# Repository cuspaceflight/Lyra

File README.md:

# Lyra

## Build Instructions
### With nix

Run
```
nix build
```
which should download the required packages and build the program, placing
the built packages in `result` by default

### Other
Requires `pico-sdk`

```
cmake -DPICO_SDK_PATH='PICO_SDK_PATH' -B build .
cmake --build build
```
which should generate `build/src/Lyra.uf2`

### Logger

The logger can be enabled through additional flags that can
be set in cmake

```
-DLOG_ENABLE=1 # Enable the Logger
-DLOG_LEVEL=LOG_LEVEL_{VERBOSE|INFO|DEBUG|ERROR|CRITICAL} # Set the logging level
-DLOG_ENABLE_COLOUR=1 # Enable colours in the output
```

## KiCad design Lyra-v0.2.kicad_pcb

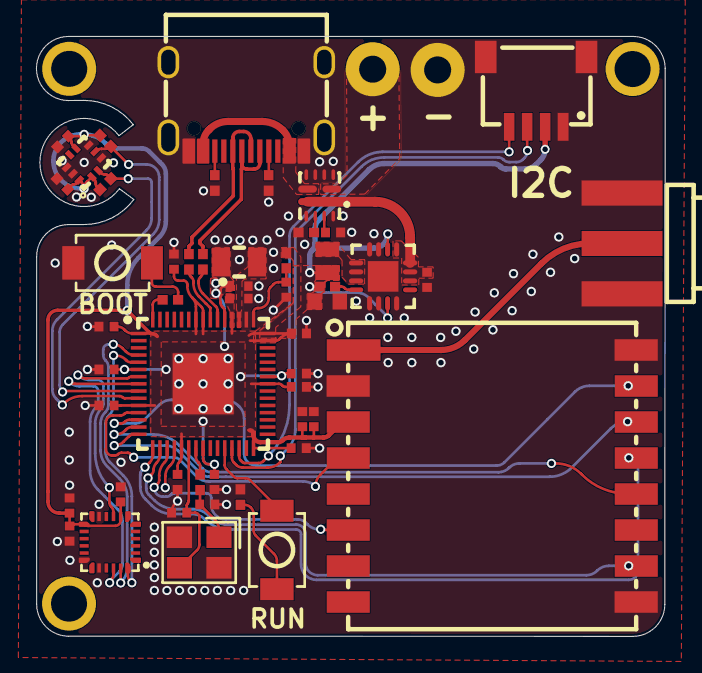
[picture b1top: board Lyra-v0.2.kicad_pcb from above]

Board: 4 copper layers, 34.9 x 33.3 mm, 54 parts (0 on the bottom side), 40 nets.

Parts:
C1, C11: 4.7uF; C0402
C2, C3, C4, C5, C6, C7, C8, C9, C10, C16, C19, C22, C23, C25: 100nF; C0402
C12, C13: 4.7uF; C0402_WIDE
C14, C15: 15pF; C0402
C17, C24: 10uF; C0402
C18: 22uF; C0603
C20: 10nF; C0402
C21: 2.2uF; C0402
CN1: QWIIC; CONN-SMD_4P-P1.00_SM04B-SRSS-TB-LF-SN
L1: 3.3uH; IND-SMD_L2.0-W1.6_AOTA-B201610S3R3-101-T
L2: RA-01SH; WIRELM-SMD_RA-01SH
L5: 2.2uH; IND-SMD_L2.0-W1.2_FTC201210S
M1, M2, M3: M2_Hole
R1: 33Ω; R0402
R2, R3, R6: 1kΩ; R0402
R4, R5: 27Ω; R0402
R7, R8: 5.1kΩ; R0402
R9: 22kΩ; R0402
R10: 100kΩ; R0402
R11, R12: 4.7kΩ; R0402
SW1, SW2: Button; SW-SMD_L3.9-W3.0-P4.45
U1: RP2354A; QFN-60_L7.0-W7.0-P0.40-TL-EP3.4
U2: ABM8-272-T3; CRYSTAL-SMD_4P-L3.2-W2.5-BL
U3: TPS2121RUXR; VQFN-HR-12_L2.5-W2.0-P0.50-BL
U4: TPS62152RGTR; TQFN-16_L3.0-W3.0-P0.50-TL-EP1.7
U5: ICM-40609-D; LGA-24_L3.0-W3.0-P0.40-TL
U6: BMP388; SENSORM-SMD_BMP388
U7: SMA-KHD9; SMA-SMD_SMA-KHD9
USBC1: USB-C 16P; USB-C_SMD-TYPE-C-31-M-12_1

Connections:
+1V1: C1.2, C2.2, C3.2, C13.2, L1.2, U1.6 (DVDD), U1.23 (DVDD), U1.39 (DVDD), U1.50 (VREG_FB)
+3V3: C4.2, C5.2, C6.2, C7.2, C8.2, C9.2, C10.2, C12.2, C18.2, C19.2, C20.2, C21.2, C22.2, C23.2, C24.2, C25.2, CN1.2, L2.3 (3.3V), L5.2, R1.1, R10.2, R11.2, R12.1, U1.1 (IOVDD), U1.11 (IOVDD), U1.20 (IOVDD), U1.30 (IOVDD), U1.38 (IOVDD), U1.44 (ADC_AVDD), U1.45 (IOVDD), U1.49 (VREG_VIN), U1.53 (USB_OTP_VDD), U1.54 (QSPI_IOVDD), U4.7 (FSW), U4.14 (VOS), U5.8 (VDDIO), U5.13 (VDD), U6.1 (VDDIO), U6.6 (CSB), U6.10 (VDD)
+5V: U3.7 (IN1), USBC1.A4B9 (VBUS), USBC1.B4A9 (VBUS)
/Power/D+: R4.2, USBC1.A6 (DP1), USBC1.B6 (DP2)
/Power/D-: R5.2, USBC1.A7 (DN1), USBC1.B7 (DN2)
/RF/LORA_BUSY: L2.10 (BUSY), U1.17 (GPIO13)
/RF/LORA_DIO1: L2.6 (DIO1), U1.18 (GPIO14)
/RF/LORA_MISO: L2.13 (MISO), U1.16 (GPIO12)
/RF/LORA_MOSI: L2.14 (MOSI), U1.15 (GPIO11)
/RF/LORA_NSS: L2.15 (NSS), U1.13 (GPIO9)
/RF/LORA_RST: L2.4 (RESET), U1.12 (GPIO8)
/RF/LORA_SCK: L2.12 (SCK), U1.14 (GPIO10)
/RP2354A/GPIO2: U1.4 (GPIO2), U5.23 (SCL/SCLK)
/RP2354A/GPIO3: U1.5 (GPIO3), U5.24 (SDA/SDI/SDIO)
/RP2354A/GPIO4: U1.7 (GPIO4), U5.9 (SDO/AD0)
/RP2354A/GPIO5: U1.8 (GPIO5), U5.22 (nCS)
/RP2354A/GPIO6: R12.2, U1.9 (GPIO6), U6.4 (SDI)
/RP2354A/GPIO7: R11.1, U1.10 (GPIO7), U6.2 (SCK)
/RP2354A/GPIO16: CN1.3, U1.27 (GPIO16)
/RP2354A/GPIO17: CN1.4, U1.28 (GPIO17)
/RP2354A/XIN: C15.1, U1.21 (XIN), U2.3
/RP2354A/XOUT: R2.2, U1.22 (XOUT)
GND: C1.1, C2.1, C3.1, C4.1, C5.1, C6.1, C7.1, C8.1, C9.1, C10.1, C11.1, C12.1, C13.1, C14.2, C15.2, C16.1, C17.1, C18.1, C19.1, C20.1, C21.1, C22.1, C23.1, C24.1, C25.1, CN1.1, CN1.5, CN1.6, L2.2 (GND), L2.9 (GND), L2.16 (GND), R3.1, R7.1, R8.1, R9.1, SW1.1, U1.47 (VREG_PGND), U1.61 (EP), U2.2 (GND), U2.4 (GND), U3.3 (CP2), U3.4 (OV2), U3.5 (OV1), U3.6 (PR1), U3.9 (ST), U3.12 (GND), U4.5 (FB), U4.6 (AGND), U4.8 (DEF), U4.15 (PGND), U4.16 (PGND), U4.17 (EP), U5.11 (RESV), U5.18 (GND), U5.20 (RESV), U6.3 (VSS), U6.5 (SDO), U6.8 (VSS), U6.9 (VSS), U7.1, U7.3, U7.4, U7.5, USBC1.1 (EH), USBC1.2 (EH), USBC1.3 (EH), USBC1.4 (EH), USBC1.A1B12 (GND), USBC1.B1A12 (GND)
unnamed: C14.1, R2.1, U2.1
unnamed: L2.1 (ANT), U7.2
unnamed: L5.1, U4.1 (SW), U4.2 (SW), U4.3 (SW)
unnamed: R3.2, SW2.1
unnamed: R6.1, SW1.2
unnamed: R6.2, U1.60 (QSPI_SS)
unnamed: SW2.2, U1.26 (RUN)
unnamed: R5.1, U1.51 (USB_DM)
unnamed: R4.1, U1.52 (USB_DP)
unnamed: C11.2, R1.2, U1.46 (VREG_AVDD)
unnamed: L1.1, U1.48 (VREG_LX)
unnamed: R9.2, U3.10 (ILM)
unnamed: C16.2, U3.11 (SS)
unnamed: R10.1, U4.4 (PG)
unnamed: R7.2, USBC1.A5 (CC1)
unnamed: R8.2, USBC1.B5 (CC2)
VDD: C17.2, U3.1 (OUT), U3.8 (OUT), U4.10 (AVIN), U4.11 (PVIN), U4.12 (PVIN), U4.13 (EN)

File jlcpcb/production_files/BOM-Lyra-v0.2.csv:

Comment,Designator,Footprint,LCSC,Quantity
100kΩ,R10,R0402,C25741,1
100nF,"C10,C16,C19,C2,C22,C23,C25,C3,C4,C5,C6,C7,C8,C9",C0402,C307331,14
10nF,C20,C0402,C15195,1
10uF,"C17,C24",C0402,C15525,2
15pF,"C14,C15",C0402,C1548,2
1kΩ,"R2,R3,R6",R0402,C11702,3
2.2uF,C21,C0402,C12530,1
2.2uH,L5,IND-SMD_L2.0-W1.2_FTC201210S,C5832324,1
22kΩ,R9,R0402,C25768,1
22uF,C18,C0603,C59461,1
27Ω,"R4,R5",R0402,C25100,2
3.3uH,L1,IND-SMD_L2.0-W1.6_AOTA-B201610S3R3-101-T,C42411119,1
33Ω,R1,R0402,C25105,1
4.7kΩ,"R11,R12",R0402,C25900,2
4.7uF,"C1,C11,C12,C13",C0402,C23733,4
5.1kΩ,"R7,R8",R0402,C25905,2
ABM8-272-T3,U2,CRYSTAL-SMD_4P-L3.2-W2.5-BL,C20625731,1
BMP388,U6,SENSORM-SMD_BMP388,C779278,1
Button,"SW1,SW2",SW-SMD_L3.9-W3.0-P4.45,C720477,2
ICM-40609-D,U5,LGA-24_L3.0-W3.0-P0.40-TL,C5360621,1
QWIIC,CN1,CONN-SMD_4P-P1.00_SM04B-SRSS-TB-LF-SN,C160404,1
RA-01SH,L2,WIRELM-SMD_RA-01SH,C2764087,1
RP2354A,U1,QFN-60_L7.0-W7.0-P0.40-TL-EP3.4,C41378174,1
SMA-KHD9,U7,SMA-SMD_SMA-KHD9,C20415780,1
TPS2121RUXR,U3,VQFN-HR-12_L2.5-W2.0-P0.50-BL,C485916,1
TPS62152RGTR,U4,TQFN-16_L3.0-W3.0-P0.50-TL-EP1.7,C2070611,1
USB-C 16P,USBC1,USB-C_SMD-TYPE-C-31-M-12_1,C165948,1

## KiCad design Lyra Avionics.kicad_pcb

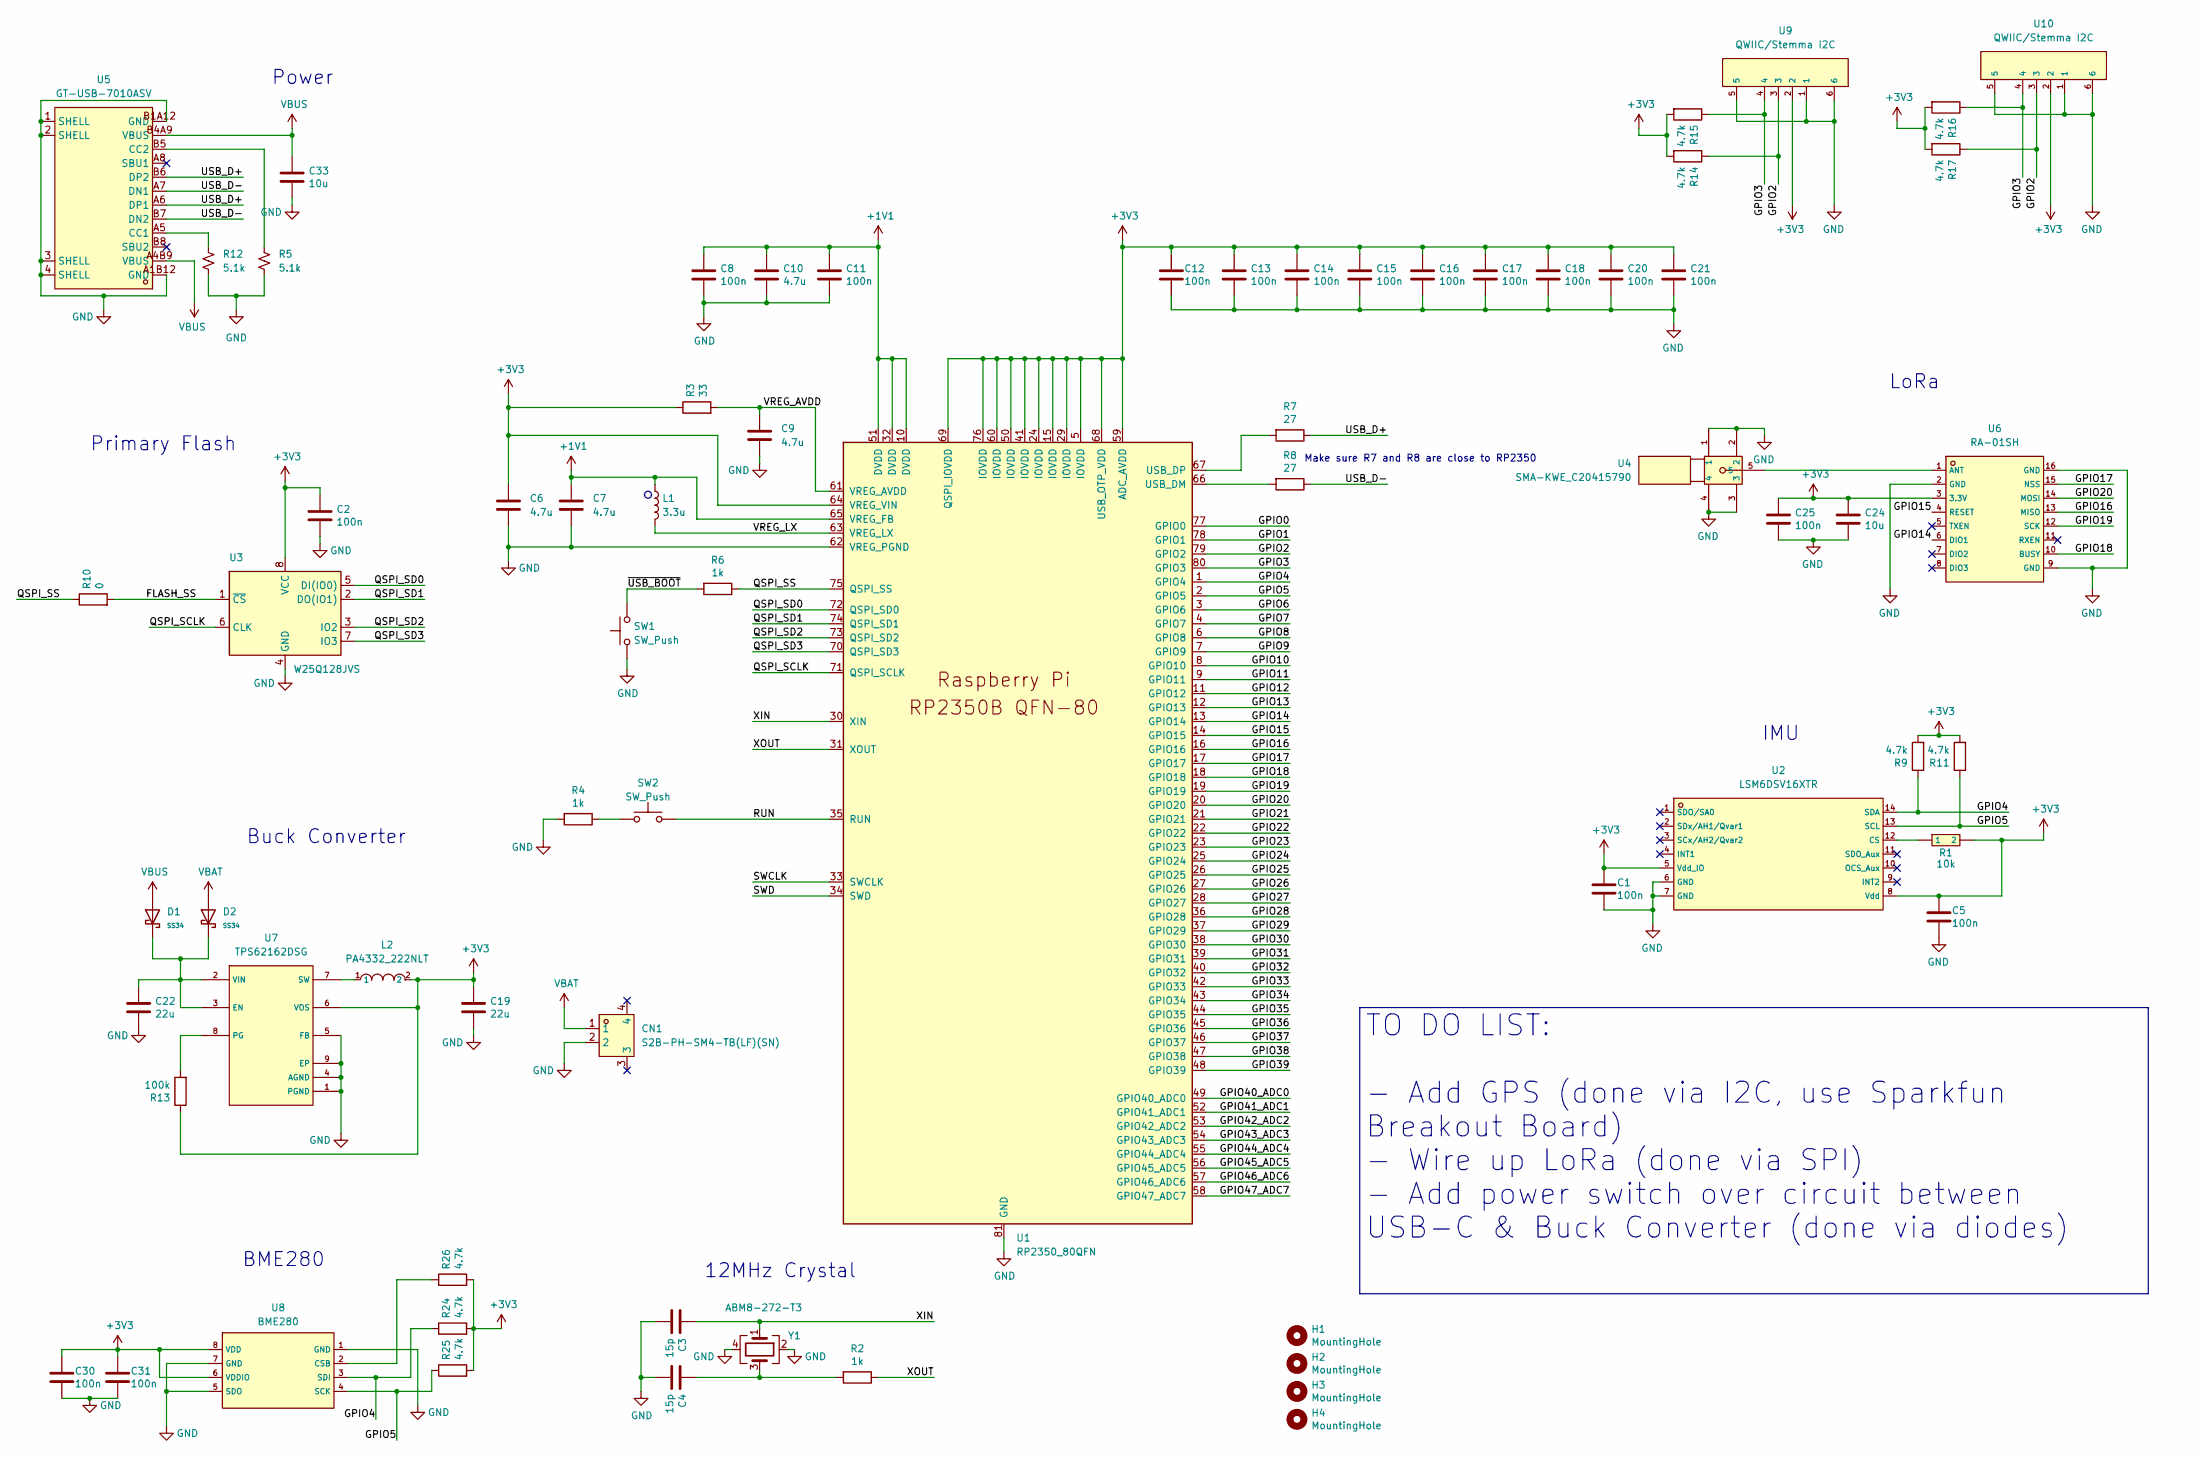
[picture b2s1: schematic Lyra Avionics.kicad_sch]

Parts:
C1, C2, C5, C8, C11, C12, C13, C14, C15, C16, C17, C18, C20, C21, C25, C30, C31: 100n; C_0402_1005Metric
C3, C4: 15p; C_0402_1005Metric
C6, C7: 4.7u; C_0402_1005Metric_small_pads
C9, C10: 4.7u; C_0402_1005Metric
C19, C22: 22u; C_0805_2012Metric
C24, C33: 10u; C_0805_2012Metric
CN1: S2B-PH-SM4-TB(LF)(SN); CONN-SMD_P2.00_S2B-PH-SM4-TB-LF-SN; LCSC Part C295747
D1, D2: SS34; D_SMA; Forward Voltage (Vf@If) 550mV@3A; Reverse Voltage (Vr) 40V; Part SS34; LCSC C8678
H1, H2, H3, H4: MountingHole; MountingHole_2.7mm_M2.5
L1: 3.3u; L_pol_2016
L2: PA4332_222NLT; IND-SMD_L4.2-W4.2_PA4332; LCSC C3222957
R1: 10k; R0402; LCSC C25744
R2, R4, R6: 1k; R_0402_1005Metric
R3: 33; R_0402_1005Metric
R5: 5.1k; R_0402
R7, R8: 27; R_0402_1005Metric
R9, R11, R14, R15, R16, R17, R24, R25, R26: 4.7k; R_0402_1005Metric
R10: 0; R_0402_1005Metric
R12: 5.1k; R_0402_1005Metric
R13: 100k; R_0402_1005Metric
SW1, SW2: SW_Push; SW_Push_1P1T_NO_Vertical_Wuerth_434133025816
U1: RP2350_80QFN; RP2350-QFN-80-1EP_10x10_P0.4mm_EP3.4x3.4mm_ThermalVias
U2: LSM6DSV16XTR; LGA-14_L3.0-W2.5-P0.50-BR; LCSC C5267406
U3: W25Q128JVS; SOIC-8_5.23x5.23mm_P1.27mm
U4: SMA-KWE_C20415790; SMA-TH_SMA-KWE; LCSC C20415790
U5: GT-USB-7010ASV; USB-C-SMD_G-SWITCH_GT-USB-7010ASV; LCSC Part C2988369
U6: RA-01SH; WIRELM-SMD_RA-01SH; LCSC C2764087
U7: TPS62162DSG; WSON-8_L2.0-W2.0-P0.50-TL-EP; LCSC C40256
U8: BME280; LGA-8_BME280_BL; LCSC C92489
U9, U10: QWIIC/Stemma I2C; CONN-SMD_4P-P1.00_SM04B-SRSS-TB-LF-SN; LCSC C160404
Y1: ABM8-272-T3; Crystal_SMD_3225-4Pin_3.2x2.5mm

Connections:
+1V1: C7.1, C8.1, C10.1, C11.1, L1.1, U1.10 (DVDD), U1.32 (DVDD), U1.51 (DVDD), U1.65 (VREG_FB)
+3V3: C1.1, C2.1, C5.1, C6.1, C12.1, C13.1, C14.1, C15.1, C16.1, C17.1, C18.1, C19.1, C20.1, C21.1, C24.1, C25.1, C30.1, C31.1, L2.2, R1.2, R3.1, R9.2, R11.2, R13.1, R14.2, R15.2, R16.2, R17.2, R24.2, R25.2, R26.2, U1.5 (IOVDD), U1.15 (IOVDD), U1.24 (IOVDD), U1.29 (IOVDD), U1.41 (IOVDD), U1.50 (IOVDD), U1.59 (ADC_AVDD), U1.60 (IOVDD), U1.64 (VREG_VIN), U1.68 (USB_OTP_VDD), U1.69 (QSPI_IOVDD), U1.76 (IOVDD), U2.5 (Vdd_IO), U2.8 (Vdd), U3.8 (VCC), U6.3 (3.3V), U7.6 (VOS), U8.6 (VDDIO), U8.8 (VDD), U9.2, U10.2
/FLASH_SS: R10.2, U3.1 (~CS)
/GPIO0: U1.77 (GPIO0)
/GPIO1: U1.78 (GPIO1)
/GPIO2: R14.1, R17.1, U1.79 (GPIO2), U9.3, U10.3
/GPIO3: R15.1, R16.1, U1.80 (GPIO3), U9.4, U10.4
/GPIO4: R9.1, R24.1, U1.1 (GPIO4), U2.14 (SDA), U8.3 (SDI)
/GPIO5: R11.1, R25.1, U1.2 (GPIO5), U2.13 (SCL), U8.4 (SCK)
/GPIO6: U1.3 (GPIO6)
/GPIO7: U1.4 (GPIO7)
/GPIO8: U1.6 (GPIO8)
/GPIO9: U1.7 (GPIO9)
/GPIO10: U1.8 (GPIO10)
/GPIO11: U1.9 (GPIO11)
/GPIO12: U1.11 (GPIO12)
/GPIO13: U1.12 (GPIO13)
/GPIO14: U1.13 (GPIO14), U6.6 (DIO1)
/GPIO15: U1.14 (GPIO15), U6.4 (RESET)
/GPIO16: U1.16 (GPIO16), U6.13 (MISO)
/GPIO17: U1.17 (GPIO17), U6.15 (NSS)
/GPIO18: U1.18 (GPIO18), U6.10 (BUSY)
/GPIO19: U1.19 (GPIO19), U6.12 (SCK)
/GPIO20: U1.20 (GPIO20), U6.14 (MOSI)
/GPIO21: U1.21 (GPIO21)
/GPIO22: U1.22 (GPIO22)
/GPIO23: U1.23 (GPIO23)
/GPIO24: U1.25 (GPIO24)
/GPIO25: U1.26 (GPIO25)
/GPIO26: U1.27 (GPIO26)
/GPIO27: U1.28 (GPIO27)
/GPIO28: U1.36 (GPIO28)
/GPIO29: U1.37 (GPIO29)
/GPIO30: U1.38 (GPIO30)
/GPIO31: U1.39 (GPIO31)
/GPIO32: U1.40 (GPIO32)
/GPIO33: U1.42 (GPIO33)
/GPIO34: U1.43 (GPIO34)
/GPIO35: U1.44 (GPIO35)
/GPIO36: U1.45 (GPIO36)
/GPIO37: U1.46 (GPIO37)
/GPIO38: U1.47 (GPIO38)
/GPIO39: U1.48 (GPIO39)
/GPIO40_ADC0: U1.49 (GPIO40_ADC0)
/GPIO41_ADC1: U1.52 (GPIO41_ADC1)
/GPIO42_ADC2: U1.53 (GPIO42_ADC2)
/GPIO43_ADC3: U1.54 (GPIO43_ADC3)
/GPIO44_ADC4: U1.55 (GPIO44_ADC4)
/GPIO45_ADC5: U1.56 (GPIO45_ADC5)
/GPIO46_ADC6: U1.57 (GPIO46_ADC6)
/GPIO47_ADC7: U1.58 (GPIO47_ADC7)
/QSPI_SCLK: U1.71 (QSPI_SCLK), U3.6 (CLK)
/QSPI_SD0: U1.72 (QSPI_SD0), U3.5 (DI(IO0))
/QSPI_SD1: U1.74 (QSPI_SD1), U3.2 (DO(IO1))
/QSPI_SD2: U1.73 (QSPI_SD2), U3.3 (IO2)
/QSPI_SD3: U1.70 (QSPI_SD3), U3.7 (IO3)
/QSPI_SS: R6.1, R10.1, U1.75 (QSPI_SS)
/RUN: SW2.2, U1.35 (RUN)
/SWCLK: U1.33 (SWCLK)
/SWD: U1.34 (SWD)
/USB_D+: R7.1, U5.A6 (DP1), U5.B6 (DP2)
/USB_D-: R8.1, U5.A7 (DN1), U5.B7 (DN2)
/VREG_AVDD: C9.1, R3.2, U1.61 (VREG_AVDD)
/VREG_LX: L1.2, U1.63 (VREG_LX)
/XIN: C3.1, U1.30 (XIN), Y1.1
/XOUT: R2.1, U1.31 (XOUT)
/~USB_BOOT: R6.2, SW1.2
GND: C1.2, C2.2, C3.2, C4.2, C5.2, C6.2, C7.2, C8.2, C9.2, C10.2, C11.2, C12.2, C13.2, C14.2, C15.2, C16.2, C17.2, C18.2, C19.2, C20.2, C21.2, C22.2, C24.2, C25.2, C30.2, C31.2, C33.2, CN1.2, R4.2, R5.1, R12.1, SW1.1, U1.62 (VREG_PGND), U1.81 (GND), U2.6 (GND), U2.7 (GND), U3.4 (GND), U4.1, U4.2, U4.3, U4.4, U5.1 (SHELL), U5.2 (SHELL), U5.3 (SHELL), U5.4 (SHELL), U5.A1B12 (GND), U5.B1A12 (GND), U6.2 (GND), U6.9 (GND), U6.16 (GND), U7.1 (PGND), U7.4 (AGND), U7.5 (FB), U7.9 (EP), U8.1 (GND), U8.5 (SDO), U8.7 (GND), U9.1, U9.5, U9.6, U10.1, U10.5, U10.6, Y1.2, Y1.4
unnamed: C4.1, R2.2, Y1.3
unnamed: R4.1, SW2.1
unnamed: R8.2, U1.66 (USB_DM)
unnamed: R7.2, U1.67 (USB_DP)
unnamed: R1.1, U2.12 (CS)
unnamed: R12.2, U5.A5 (CC1)
unnamed: R5.2, U5.B5 (CC2)
unnamed: U4.5, U6.1 (ANT)
unnamed: C22.1, D1.1, D2.1, U7.2 (VIN), U7.3 (EN)
unnamed: R13.2, U7.8 (PG)
unnamed: L2.1, U7.7 (SW)
unnamed: R26.1, U8.2 (CSB)
VBAT: CN1.1, D2.2
VBUS: C33.1, D1.2, U5.A4B9 (VBUS), U5.B4A9 (VBUS)

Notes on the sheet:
12MHz Crystal
Buck Converter
LoRa
Primary Flash
Make sure R7 and R8 are close to RP2350
Power
BME280
IMU
TO DO LIST: - Add GPS (done via I2C, use Sparkfun Breakout Board) - Wire up LoRa (done via SPI) - Add power switch over circuit between USB-C & Buck Converter (done via diodes)

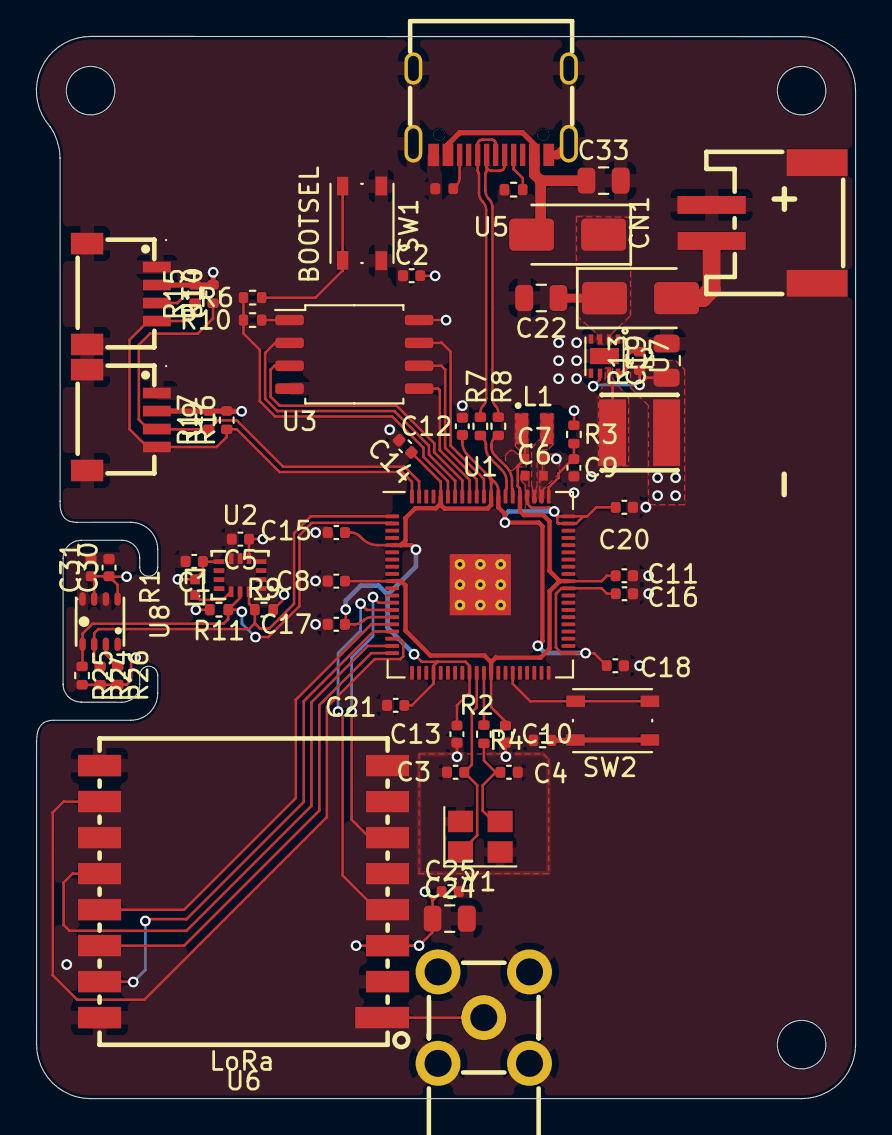
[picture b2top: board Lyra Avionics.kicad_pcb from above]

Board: 4 copper layers, 45.5 x 59.0 mm, 68 parts (0 on the bottom side), 43 nets.

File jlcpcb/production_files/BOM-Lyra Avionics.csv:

Comment,Designator,Footprint,LCSC,Quantity
0,R10,R_0402_1005Metric,C17168,1
100k,R13,R_0402_1005Metric,C25741,1
100n,"C1,C11,C12,C13,C14,C15,C16,C17,C18,C2,C20,C21,C25,C30,C31,C5,C8",C_0402_1005Metric,C1525,17
10k,R1,R0402,C25744,1
10u,"C24,C33",C_0805_2012Metric,C15850,2
15p,"C3,C4",C_0402_1005Metric,C1548,2
1k,"R2,R4,R6",R_0402_1005Metric,C11702,3
22u,"C19,C22",C_0805_2012Metric,C45783,2
27,"R7,R8",R_0402_1005Metric,C25100,2
3.3u,L1,L_pol_2016,C42411119,1
33,R3,R_0402_1005Metric,C25105,1
4.7k,"R11,R14,R15,R16,R17,R24,R25,R26,R9",R_0402_1005Metric,C25900,9
4.7u,"C10,C6,C7,C9",C_0402_1005Metric,C23733,4
5.1k,"R12,R5",R_0402_1005Metric,C25905,2
ABM8-272-T3,Y1,Crystal_SMD_3225-4Pin_3.2x2.5mm,C20625731,1
BME280,U8,LGA-8_BME280_BL,C92489,1
GT-USB-7010ASV,U5,USB-C-SMD_G-SWITCH_GT-USB-7010ASV,C2988369,1
LSM6DSV16XTR,U2,LGA-14_L3.0-W2.5-P0.50-BR,C5267406,1
PA4332_222NLT,L2,IND-SMD_L4.2-W4.2_PA4332,C3222957,1
QWIIC/Stemma I2C,"U10,U9",CONN-SMD_4P-P1.00_SM04B-SRSS-TB-LF-SN,C160404,2
RA-01SH,U6,WIRELM-SMD_RA-01SH,C2764087,1
RP2350_80QFN,U1,RP2350-QFN-80-1EP_10x10_P0.4mm_EP3.4x3.4mm_ThermalVias,C42415655,1
S2B-PH-SM4-TB(LF)(SN),CN1,CONN-SMD_P2.00_S2B-PH-SM4-TB-LF-SN,C295747,1
SMA-KWE_C20415790,U4,SMA-TH_SMA-KWE,C20415790,1
SS34,"D1,D2",D_SMA,C8678,2
SW_Push,"SW1,SW2",SW_Push_1P1T_NO_Vertical_Wuerth_434133025816,C5504987,2
TPS62162DSG,U7,WSON-8_L2.0-W2.0-P0.50-TL-EP,C40256,1
W25Q128JVS,U3,SOIC-8_5.23x5.23mm_P1.27mm,C97521,1
MountingHole,H1,MountingHole_2.7mm_M2.5,,1
MountingHole,H2,MountingHole_2.7mm_M2.5,,1
MountingHole,H3,MountingHole_2.7mm_M2.5,,1

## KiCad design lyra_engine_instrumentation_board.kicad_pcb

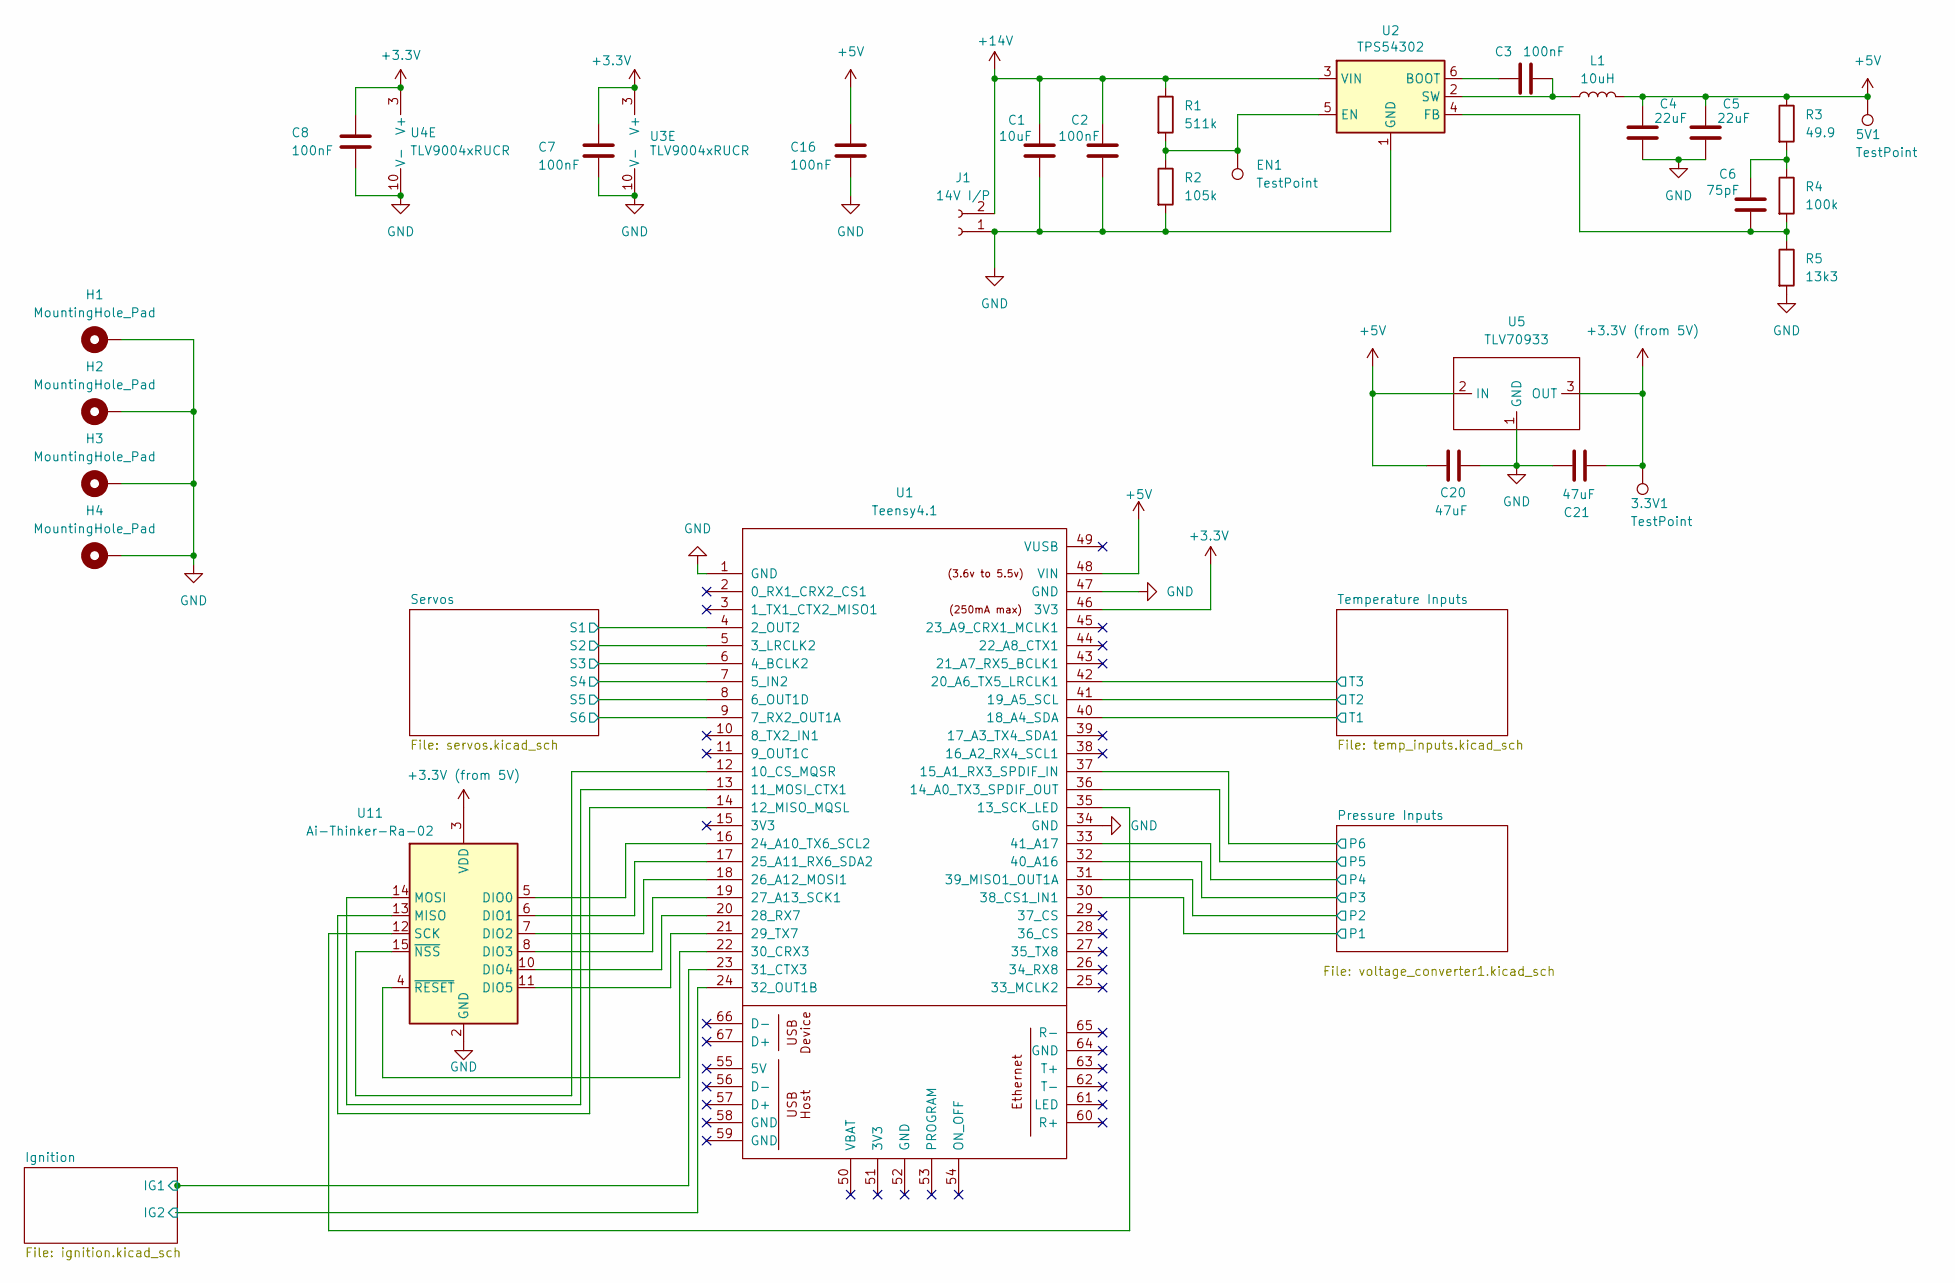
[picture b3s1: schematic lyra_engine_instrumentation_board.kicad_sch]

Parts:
3.3V1, 5V1: TestPoint; TestPoint_Pad_D1.0mm
C1: 10uF; C_0603_1608Metric_Pad1.08x0.95mm_HandSolder
C2, C3: 100nF; C_0603_1608Metric_Pad1.08x0.95mm_HandSolder
C4, C5: 22uF; C_0603_1608Metric_Pad1.08x0.95mm_HandSolder
C6: 75pF; C_0603_1608Metric_Pad1.08x0.95mm_HandSolder
C7, C8, C16: 100nF; Fuse_1206_3216Metric_Pad1.42x1.75mm_HandSolder
C20, C21: 47uF; C_0603_1608Metric_Pad1.08x0.95mm_HandSolder
EN1: TestPoint; TestPoint_Pad_D1.0mm
H1, H2, H3, H4: MountingHole_Pad; MountingHole_2.2mm_M2_Pad_TopOnly
J1: 14V I/P; Molex_Nano-Fit_105309-xx02_1x02_P2.50mm_Vertical
L1: 10uH; L_Bourns_SRN6045TA
R1: 511k; R_0603_1608Metric_Pad0.98x0.95mm_HandSolder
R2: 105k; R_0603_1608Metric_Pad0.98x0.95mm_HandSolder
R3: 49.9; R_0603_1608Metric_Pad0.98x0.95mm_HandSolder
R4: 100k; R_0603_1608Metric_Pad0.98x0.95mm_HandSolder
R5: 13k3; R_0603_1608Metric_Pad0.98x0.95mm_HandSolder
U1: Teensy4.1; Teensy41
U2: TPS54302; SOT-23-6; MPN TI TPS54302DDC; LCSC C129370
U3, U4: TLV9004xRUCR; Texas_S-PX2QFN-14
U5: TLV70933; SOT-89-3_Handsoldering
U11: Ai-Thinker-Ra-02; Ai-Thinker-Ra-01-LoRa

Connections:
+3.3V: C7.1, C8.2, U1.46 (3V3), U3.3 (V+), U4.3 (V+); also elsewhere on the board
+3.3V (from 5V): 3.3V1.1, C21.2, U5.3 (OUT), U11.3 (VDD)
+5V: 5V1.1, C4.1, C5.1, C16.1, C20.1, L1.2, R3.1, U1.48 (VIN), U5.2 (IN); also elsewhere on the board
+14V: C1.1, C2.1, J1.2, R1.1, U2.3 (VIN); also elsewhere on the board
/Ignition/IG1: U1.23 (31_CTX3); also elsewhere on the board
/Ignition/IG2: U1.24 (32_OUT1B); also elsewhere on the board
/Pressure Inputs/P1: U1.30 (38_CS1_IN1); also elsewhere on the board
/Pressure Inputs/P2: U1.31 (39_MISO1_OUT1A); also elsewhere on the board
/Pressure Inputs/P3: U1.32 (40_A16); also elsewhere on the board
/Pressure Inputs/P4: U1.33 (41_A17); also elsewhere on the board
/Pressure Inputs/P5: U1.36 (14_A0_TX3_SPDIF_OUT); also elsewhere on the board
/Pressure Inputs/P6: U1.37 (15_A1_RX3_SPDIF_IN); also elsewhere on the board
/Servos/S1: U1.4 (2_OUT2); also elsewhere on the board
/Servos/S2: U1.5 (3_LRCLK2); also elsewhere on the board
/Servos/S3: U1.6 (4_BCLK2); also elsewhere on the board
/Servos/S4: U1.7 (5_IN2); also elsewhere on the board
/Servos/S5: U1.8 (6_OUT1D); also elsewhere on the board
/Servos/S6: U1.9 (7_RX2_OUT1A); also elsewhere on the board
/Temperature Inputs/T1: U1.40 (18_A4_SDA); also elsewhere on the board
/Temperature Inputs/T2: U1.41 (19_A5_SCL); also elsewhere on the board
/Temperature Inputs/T3: U1.42 (20_A6_TX5_LRCLK1); also elsewhere on the board
GND: C1.2, C2.2, C4.2, C5.2, C7.2, C8.1, C16.2, C20.2, C21.1, H1.1, H2.1, H3.1, H4.1, J1.1, R2.2, R5.2, U1.1 (GND), U1.34 (GND), U1.47 (GND), U2.1 (GND), U3.10 (V-), U4.10 (V-), U5.1 (GND), U11.1 (GND), U11.2 (GND), U11.9 (GND), U11.16 (GND); also elsewhere on the board
unnamed: C6.1, R3.2, R4.1
unnamed: U1.12 (10_CS_MQSR), U11.15 (~NSS)
unnamed: U1.13 (11_MOSI_CTX1), U11.14 (MOSI)
unnamed: U1.14 (12_MISO_MQSL), U11.13 (MISO)
unnamed: U1.35 (13_SCK_LED), U11.12 (SCK)
unnamed: U1.16 (24_A10_TX6_SCL2), U11.5 (DIO0)
unnamed: U1.17 (25_A11_RX6_SDA2), U11.6 (DIO1)
unnamed: U1.18 (26_A12_MOSI1), U11.7 (DIO2)
unnamed: U1.19 (27_A13_SCK1), U11.8 (DIO3)
unnamed: U1.20 (28_RX7), U11.10 (DIO4)
unnamed: U1.21 (29_TX7), U11.11 (DIO5)
unnamed: U1.22 (30_CRX3), U11.4 (~RESET)
unnamed: C3.1, U2.6 (BOOT)
unnamed: EN1.1, R1.2, R2.1, U2.5 (EN)
unnamed: C6.2, R4.2, R5.1, U2.4 (FB)
unnamed: C3.2, L1.1, U2.2 (SW)

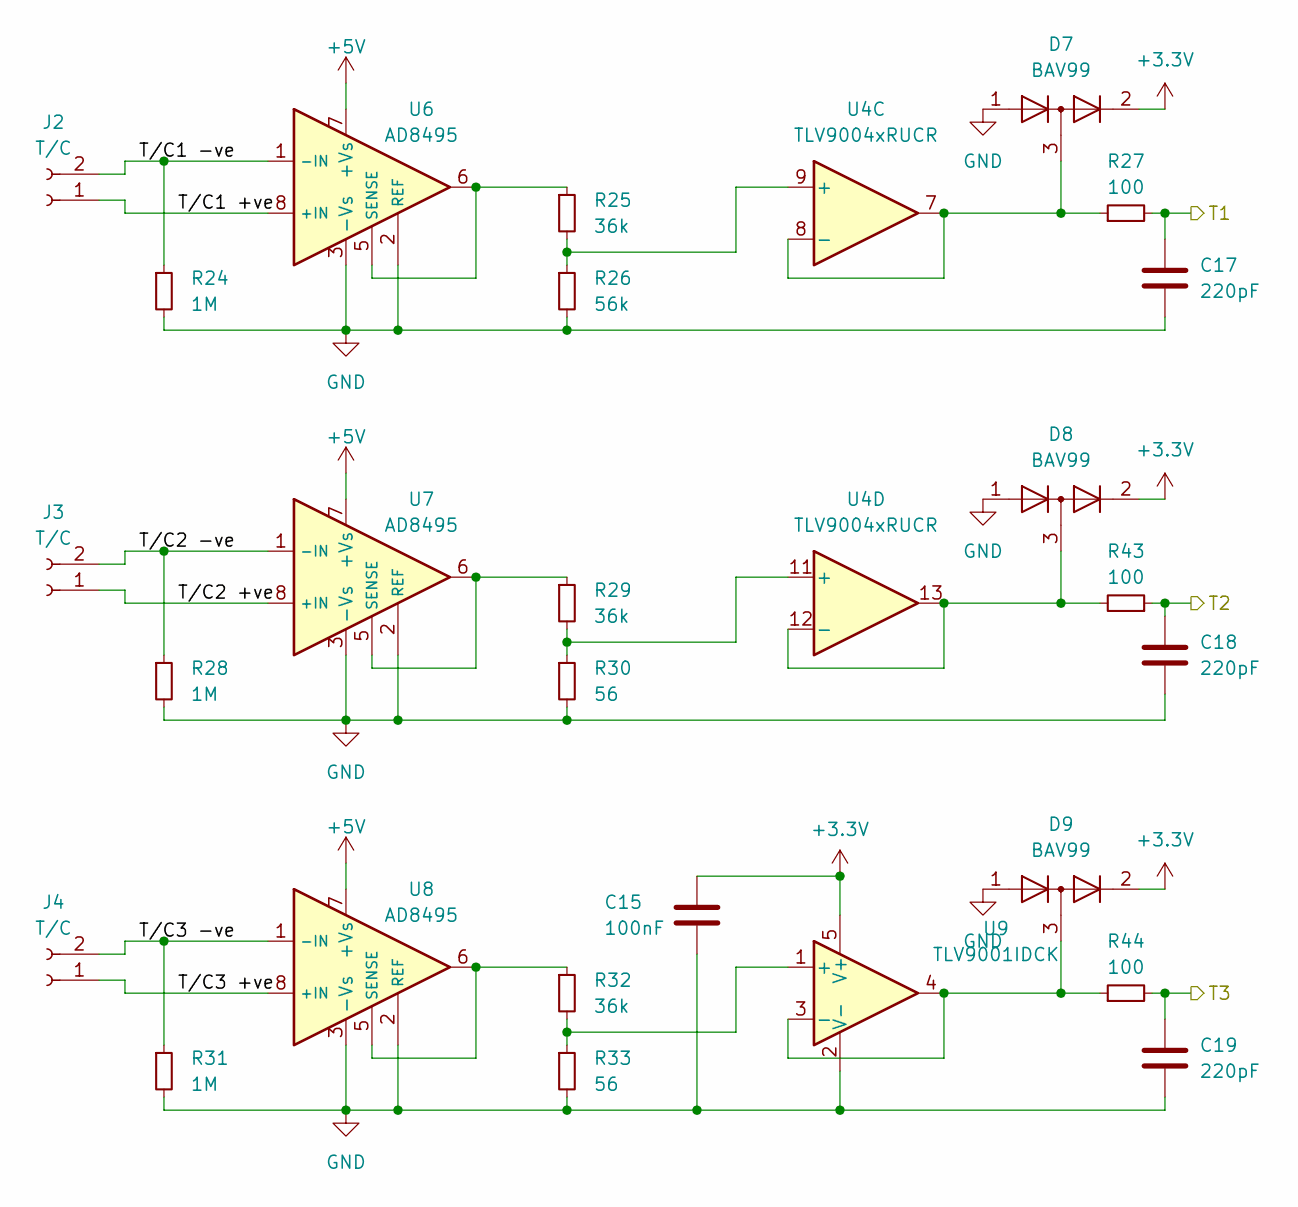
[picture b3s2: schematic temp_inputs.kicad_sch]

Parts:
C15: 100nF; Fuse_1206_3216Metric_Pad1.42x1.75mm_HandSolder
C17, C18, C19: 220pF; Fuse_1206_3216Metric_Pad1.42x1.75mm_HandSolder
D7, D8, D9: BAV99; SOT-23
J2, J3, J4: T/C; Molex_Nano-Fit_105309-xx02_1x02_P2.50mm_Vertical
R24, R28, R31: 1M; R_1206_3216Metric_Pad1.30x1.75mm_HandSolder
R25, R29, R32: 36k; R_1206_3216Metric_Pad1.30x1.75mm_HandSolder
R26: 56k; R_1206_3216Metric_Pad1.30x1.75mm_HandSolder
R27, R43, R44: 100; R_1206_3216Metric_Pad1.30x1.75mm_HandSolder
R30, R33: 56; R_1206_3216Metric_Pad1.30x1.75mm_HandSolder
U4: TLV9004xRUCR; Texas_S-PX2QFN-14
U6, U7, U8: AD8495; MSOP-8_3x3mm_P0.65mm
U9: TLV9001IDCK; SOT-353_SC-70-5

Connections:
+3.3V: C15.2, D7.2 (A), D8.2 (A), D9.2 (A), U9.5 (V+); also elsewhere on the board
+5V: U6.7 (+Vs), U7.7 (+Vs), U8.7 (+Vs); also elsewhere on the board
/Temperature Inputs/T1: C17.2, R27.2; also elsewhere on the board
/Temperature Inputs/T2: C18.2, R43.1; also elsewhere on the board
/Temperature Inputs/T3: C19.2, R44.2; also elsewhere on the board
/Temperature Inputs/T/C1 +ve: J2.1, U6.8 (+IN)
/Temperature Inputs/T/C1 -ve: J2.2, R24.1, U6.1 (-IN)
/Temperature Inputs/T/C2 +ve: J3.1, U7.8 (+IN)
/Temperature Inputs/T/C2 -ve: J3.2, R28.1, U7.1 (-IN)
/Temperature Inputs/T/C3 +ve: J4.1, U8.8 (+IN)
/Temperature Inputs/T/C3 -ve: J4.2, R31.1, U8.1 (-IN)
GND: C15.1, C17.1, C18.1, C19.1, D7.1 (K), D8.1 (K), D9.1 (K), R24.2, R26.2, R28.2, R30.2, R31.2, R33.2, U6.2 (REF), U6.3 (-Vs), U7.2 (REF), U7.3 (-Vs), U8.2 (REF), U8.3 (-Vs), U9.2 (V-); also elsewhere on the board
unnamed: R25.2, R26.1, U4.9 (+)
unnamed: D7.3 (K), R27.1, U4.7, U4.8 (-)
unnamed: R29.2, R30.1, U4.11 (+)
unnamed: D8.3 (K), R43.2, U4.12 (-), U4.13
unnamed: R25.1, U6.5 (SENSE), U6.6
unnamed: R29.1, U7.5 (SENSE), U7.6
unnamed: R32.1, U8.5 (SENSE), U8.6
unnamed: R32.2, R33.1, U9.1 (+)
unnamed: D9.3 (K), R44.1, U9.3 (-), U9.4

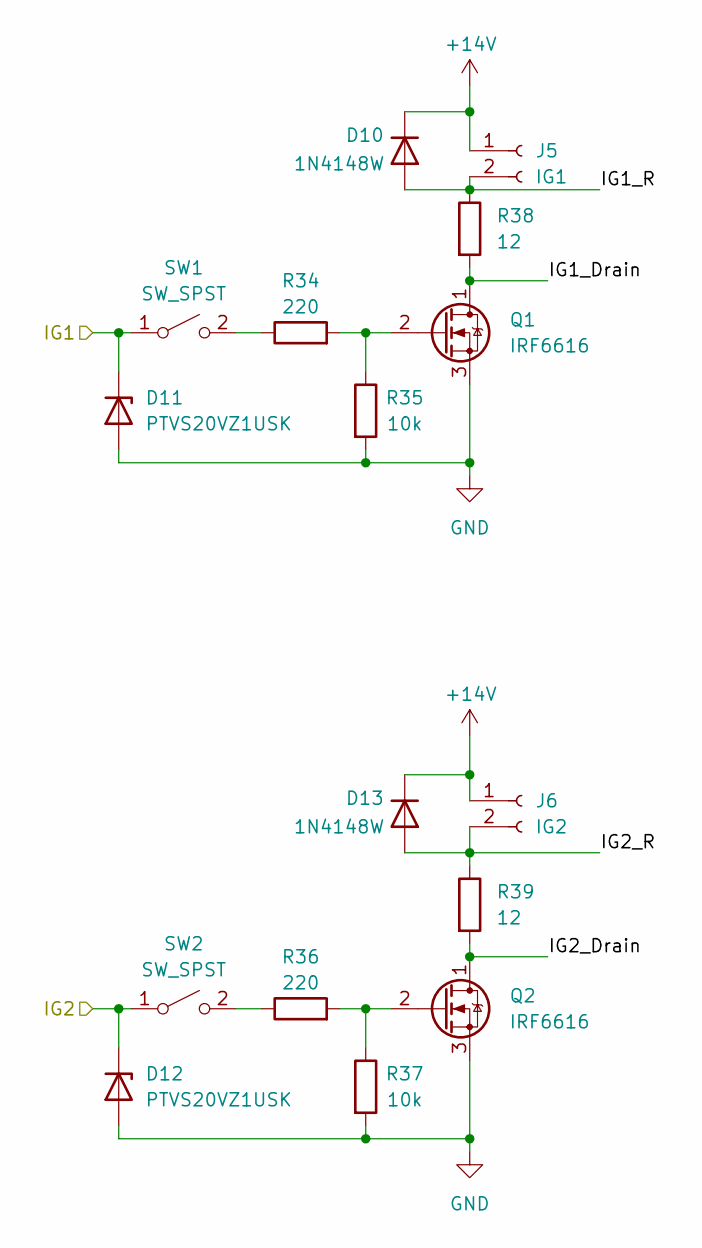
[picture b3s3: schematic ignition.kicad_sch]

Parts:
D10, D13: 1N4148W; D_SOD-123
D11, D12: PTVS20VZ1USK; Nexperia_DSN1608-2_1.6x0.8mm
J5: IG1; Molex_Nano-Fit_105309-xx02_1x02_P2.50mm_Vertical
J6: IG2; Molex_Nano-Fit_105309-xx02_1x02_P2.50mm_Vertical
Q1, Q2: IRF6616; DirectFET_MX
R34, R36: 220; R_1206_3216Metric_Pad1.30x1.75mm_HandSolder
R35, R37: 10k; R_1206_3216Metric_Pad1.30x1.75mm_HandSolder
R38, R39: 12; R_1206_3216Metric_Pad1.30x1.75mm_HandSolder
SW1, SW2: SW_SPST; SW_DIP_SPSTx01_Slide_6.7x4.1mm_W7.62mm_P2.54mm_LowProfile

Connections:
+14V: D10.1 (K), D13.1 (K), J5.1, J6.1; also elsewhere on the board
/Ignition/IG1: D11.1 (K), SW1.1 (A); also elsewhere on the board
/Ignition/IG1_Drain: Q1.1 (D), R38.2
/Ignition/IG1_R: D10.2 (A), J5.2, R38.1
/Ignition/IG2: D12.1 (K), SW2.1 (A); also elsewhere on the board
/Ignition/IG2_Drain: Q2.1 (D), R39.2
/Ignition/IG2_R: D13.2 (A), J6.2, R39.1
GND: D11.2 (A), D12.2 (A), Q1.3 (S), Q2.3 (S), R35.2, R37.2; also elsewhere on the board
unnamed: Q1.2 (G), R34.2, R35.1
unnamed: Q2.2 (G), R36.2, R37.1
unnamed: R34.1, SW1.2 (B)
unnamed: R36.1, SW2.2 (B)

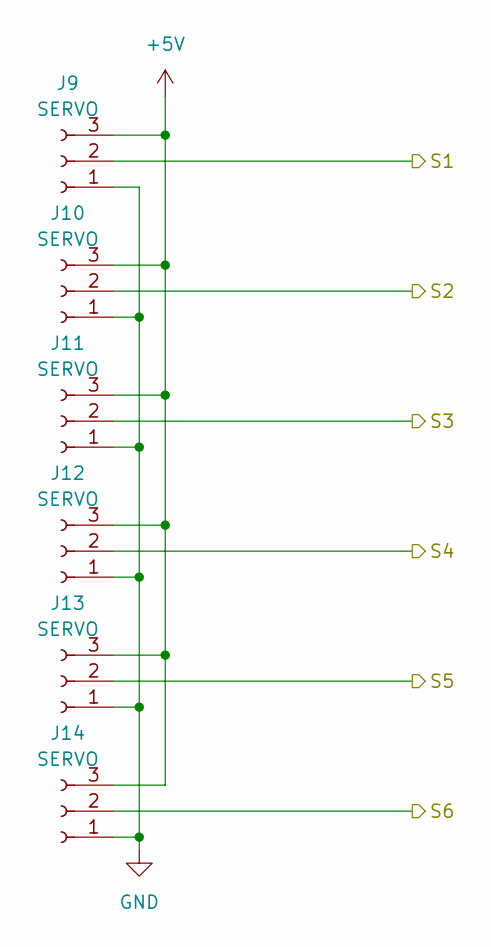
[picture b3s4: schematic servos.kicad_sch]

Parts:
J9, J10, J11, J12, J13, J14: SERVO; Molex_Nano-Fit_105309-xx03_1x03_P2.50mm_Vertical

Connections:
+5V: J9.3, J10.3, J11.3, J12.3, J13.3, J14.3; also elsewhere on the board
/Servos/S1: J9.2; also elsewhere on the board
/Servos/S2: J10.2; also elsewhere on the board
/Servos/S3: J11.2; also elsewhere on the board
/Servos/S4: J12.2; also elsewhere on the board
/Servos/S5: J13.2; also elsewhere on the board
/Servos/S6: J14.2; also elsewhere on the board
GND: J9.1, J10.1, J11.1, J12.1, J13.1, J14.1; also elsewhere on the board
